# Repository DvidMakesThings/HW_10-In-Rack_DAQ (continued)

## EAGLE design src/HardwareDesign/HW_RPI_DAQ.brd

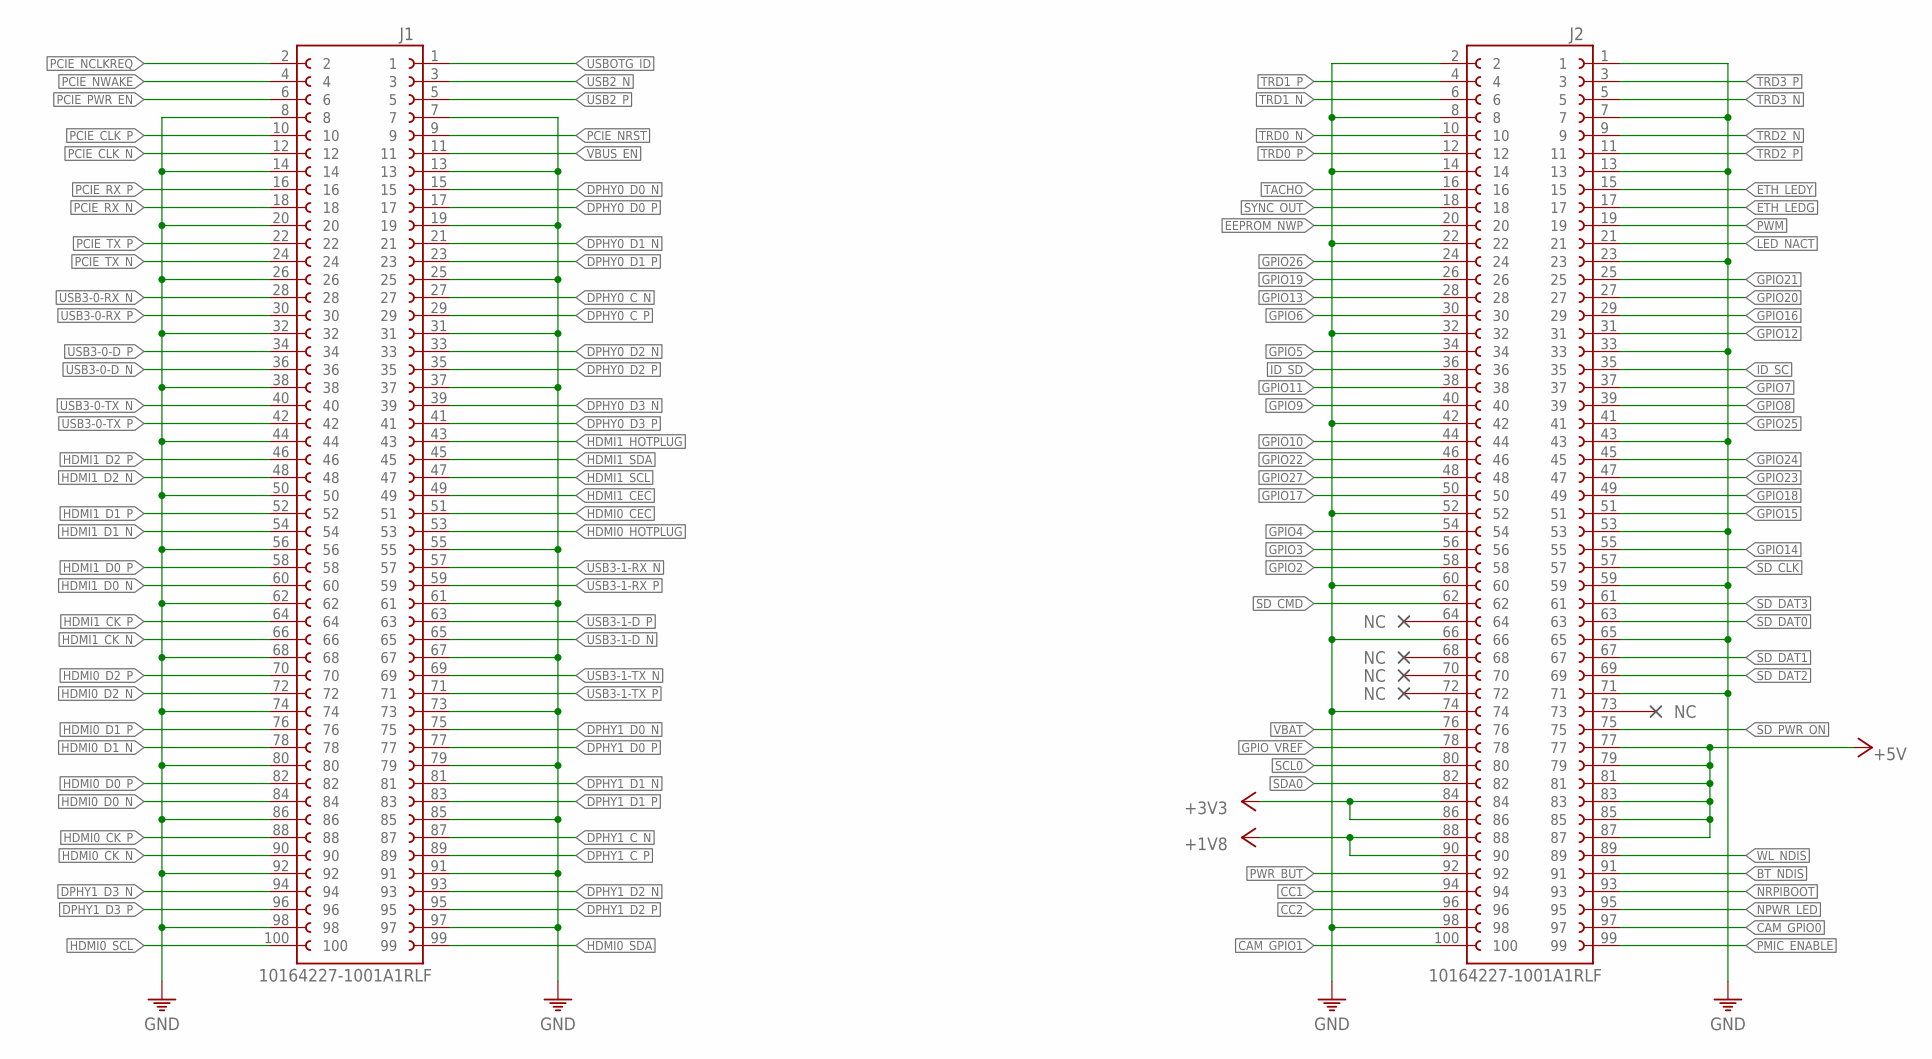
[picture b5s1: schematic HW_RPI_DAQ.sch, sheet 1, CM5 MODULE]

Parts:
J1, J2: 10164227-1001A1RLF; AMPHENOL_10164227-1001A1RLF

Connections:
+1V8: J2.88, J2.90; also elsewhere on the board
+3V3: J2.84, J2.86; also elsewhere on the board
+5V: J2.77, J2.79, J2.81, J2.83, J2.85, J2.87; also elsewhere on the board
BT_NDIS: J2.91; also elsewhere on the board
CAM_GPIO0: J2.97; also elsewhere on the board
CAM_GPIO1: J2.100; also elsewhere on the board
CC1: J2.94; also elsewhere on the board
CC2: J2.96; also elsewhere on the board
DPHY0_C_N: J1.27; also elsewhere on the board
DPHY0_C_P: J1.29; also elsewhere on the board
DPHY0_D0_N: J1.15; also elsewhere on the board
DPHY0_D0_P: J1.17; also elsewhere on the board
DPHY0_D1_N: J1.21; also elsewhere on the board
DPHY0_D1_P: J1.23; also elsewhere on the board
DPHY0_D2_N: J1.33; also elsewhere on the board
DPHY0_D2_P: J1.35; also elsewhere on the board
DPHY0_D3_N: J1.39; also elsewhere on the board
DPHY0_D3_P: J1.41; also elsewhere on the board
DPHY1_C_N: J1.87; also elsewhere on the board
DPHY1_C_P: J1.89; also elsewhere on the board
DPHY1_D0_N: J1.75; also elsewhere on the board
DPHY1_D0_P: J1.77; also elsewhere on the board
DPHY1_D1_N: J1.81; also elsewhere on the board
DPHY1_D1_P: J1.83; also elsewhere on the board
DPHY1_D2_N: J1.93; also elsewhere on the board
DPHY1_D2_P: J1.95; also elsewhere on the board
DPHY1_D3_N: J1.94; also elsewhere on the board
DPHY1_D3_P: J1.96; also elsewhere on the board
EEPROM_NWP: J2.20; also elsewhere on the board
ETH_LEDG: J2.17; also elsewhere on the board
ETH_LEDY: J2.15; also elsewhere on the board
GND: J1.7, J1.8, J1.13, J1.14, J1.19, J1.20, J1.25, J1.26, J1.31, J1.32, J1.37, J1.38, J1.44, J1.50, J1.55, J1.56, J1.61, J1.62, J1.67, J1.68, J1.73, J1.74, J1.79, J1.80, J1.85, J1.86, J1.91, J1.92, J1.97, J1.98, J2.1, J2.2, J2.7, J2.8, J2.13, J2.14, J2.22, J2.23, J2.32, J2.33, J2.42, J2.43, J2.52, J2.53, J2.59, J2.60, J2.65, J2.66, J2.71, J2.74, J2.98; also elsewhere on the board
GPIO2: J2.58; also elsewhere on the board
GPIO3: J2.56; also elsewhere on the board
GPIO4: J2.54; also elsewhere on the board
GPIO5: J2.34; also elsewhere on the board
GPIO6: J2.30; also elsewhere on the board
GPIO7: J2.37; also elsewhere on the board
GPIO8: J2.39; also elsewhere on the board
GPIO9: J2.40; also elsewhere on the board
GPIO10: J2.44; also elsewhere on the board
GPIO11: J2.38; also elsewhere on the board
GPIO12: J2.31; also elsewhere on the board
GPIO13: J2.28; also elsewhere on the board
GPIO14: J2.55; also elsewhere on the board
GPIO15: J2.51; also elsewhere on the board
GPIO16: J2.29; also elsewhere on the board
GPIO17: J2.50; also elsewhere on the board
GPIO18: J2.49; also elsewhere on the board
GPIO19: J2.26; also elsewhere on the board
GPIO20: J2.27; also elsewhere on the board
GPIO21: J2.25; also elsewhere on the board
GPIO22: J2.46; also elsewhere on the board
GPIO23: J2.47; also elsewhere on the board
GPIO24: J2.45; also elsewhere on the board
GPIO25: J2.41; also elsewhere on the board
GPIO26: J2.24; also elsewhere on the board
GPIO27: J2.48; also elsewhere on the board
GPIO_VREF: J2.78; also elsewhere on the board
HDMI0_CEC: J1.51; also elsewhere on the board
HDMI0_CK_N: J1.90; also elsewhere on the board
HDMI0_CK_P: J1.88; also elsewhere on the board
HDMI0_D0_N: J1.84; also elsewhere on the board
HDMI0_D0_P: J1.82; also elsewhere on the board
HDMI0_D1_N: J1.78; also elsewhere on the board
HDMI0_D1_P: J1.76; also elsewhere on the board
HDMI0_D2_N: J1.72; also elsewhere on the board
HDMI0_D2_P: J1.70; also elsewhere on the board
HDMI0_HOTPLUG: J1.53; also elsewhere on the board
HDMI0_SCL: J1.100; also elsewhere on the board
HDMI0_SDA: J1.99; also elsewhere on the board
HDMI1_CEC: J1.49; also elsewhere on the board
HDMI1_CK_N: J1.66; also elsewhere on the board
HDMI1_CK_P: J1.64; also elsewhere on the board
HDMI1_D0_N: J1.60; also elsewhere on the board
HDMI1_D0_P: J1.58; also elsewhere on the board
HDMI1_D1_N: J1.54; also elsewhere on the board
HDMI1_D1_P: J1.52; also elsewhere on the board
HDMI1_D2_N: J1.48; also elsewhere on the board
HDMI1_D2_P: J1.46; also elsewhere on the board
HDMI1_HOTPLUG: J1.43; also elsewhere on the board
HDMI1_SCL: J1.47; also elsewhere on the board
HDMI1_SDA: J1.45; also elsewhere on the board
ID_SC: J2.35; also elsewhere on the board
ID_SD: J2.36; also elsewhere on the board
LED_NACT: J2.21
NPWR_LED: J2.95; also elsewhere on the board
NRPIBOOT: J2.93; also elsewhere on the board
PCIE_CLK_N: J1.12; also elsewhere on the board
PCIE_CLK_P: J1.10; also elsewhere on the board
PCIE_NCLKREQ: J1.2; also elsewhere on the board
PCIE_NRST: J1.9; also elsewhere on the board
PCIE_NWAKE: J1.4; also elsewhere on the board
PCIE_PWR_EN: J1.6; also elsewhere on the board
PCIE_RX_N: J1.18; also elsewhere on the board
PCIE_RX_P: J1.16; also elsewhere on the board
PCIE_TX_N: J1.24; also elsewhere on the board
PCIE_TX_P: J1.22; also elsewhere on the board
PMIC_ENABLE: J2.99; also elsewhere on the board
PWM: J2.19; also elsewhere on the board
PWR_BUT: J2.92; also elsewhere on the board
SCL0: J2.80; also elsewhere on the board
SDA0: J2.82; also elsewhere on the board
SD_CLK: J2.57; also elsewhere on the board
SD_CMD: J2.62; also elsewhere on the board
SD_DAT0: J2.63; also elsewhere on the board
SD_DAT1: J2.67; also elsewhere on the board
SD_DAT2: J2.69; also elsewhere on the board
SD_DAT3: J2.61; also elsewhere on the board
SD_PWR_ON: J2.75; also elsewhere on the board
SYNC_OUT: J2.18; also elsewhere on the board
TACHO: J2.16; also elsewhere on the board
TRD0_N: J2.10; also elsewhere on the board
TRD0_P: J2.12; also elsewhere on the board
TRD1_N: J2.6; also elsewhere on the board
TRD1_P: J2.4; also elsewhere on the board
TRD2_N: J2.9; also elsewhere on the board
TRD2_P: J2.11; also elsewhere on the board
TRD3_N: J2.5; also elsewhere on the board
TRD3_P: J2.3; also elsewhere on the board
USB2_N: J1.3; also elsewhere on the board
USB2_P: J1.5; also elsewhere on the board
USB3-0-D_N: J1.36; also elsewhere on the board
USB3-0-D_P: J1.34; also elsewhere on the board
USB3-0-RX_N: J1.28; also elsewhere on the board
USB3-0-RX_P: J1.30; also elsewhere on the board
USB3-0-TX_N: J1.40; also elsewhere on the board
USB3-0-TX_P: J1.42; also elsewhere on the board
USB3-1-D_N: J1.65; also elsewhere on the board
USB3-1-D_P: J1.63; also elsewhere on the board
USB3-1-RX_N: J1.57; also elsewhere on the board
USB3-1-RX_P: J1.59; also elsewhere on the board
USB3-1-TX_N: J1.69; also elsewhere on the board
USB3-1-TX_P: J1.71; also elsewhere on the board
USBOTG_ID: J1.1; also elsewhere on the board
VBAT: J2.76; also elsewhere on the board
VBUS_EN: J1.11; also elsewhere on the board
WL_NDIS: J2.89; also elsewhere on the board

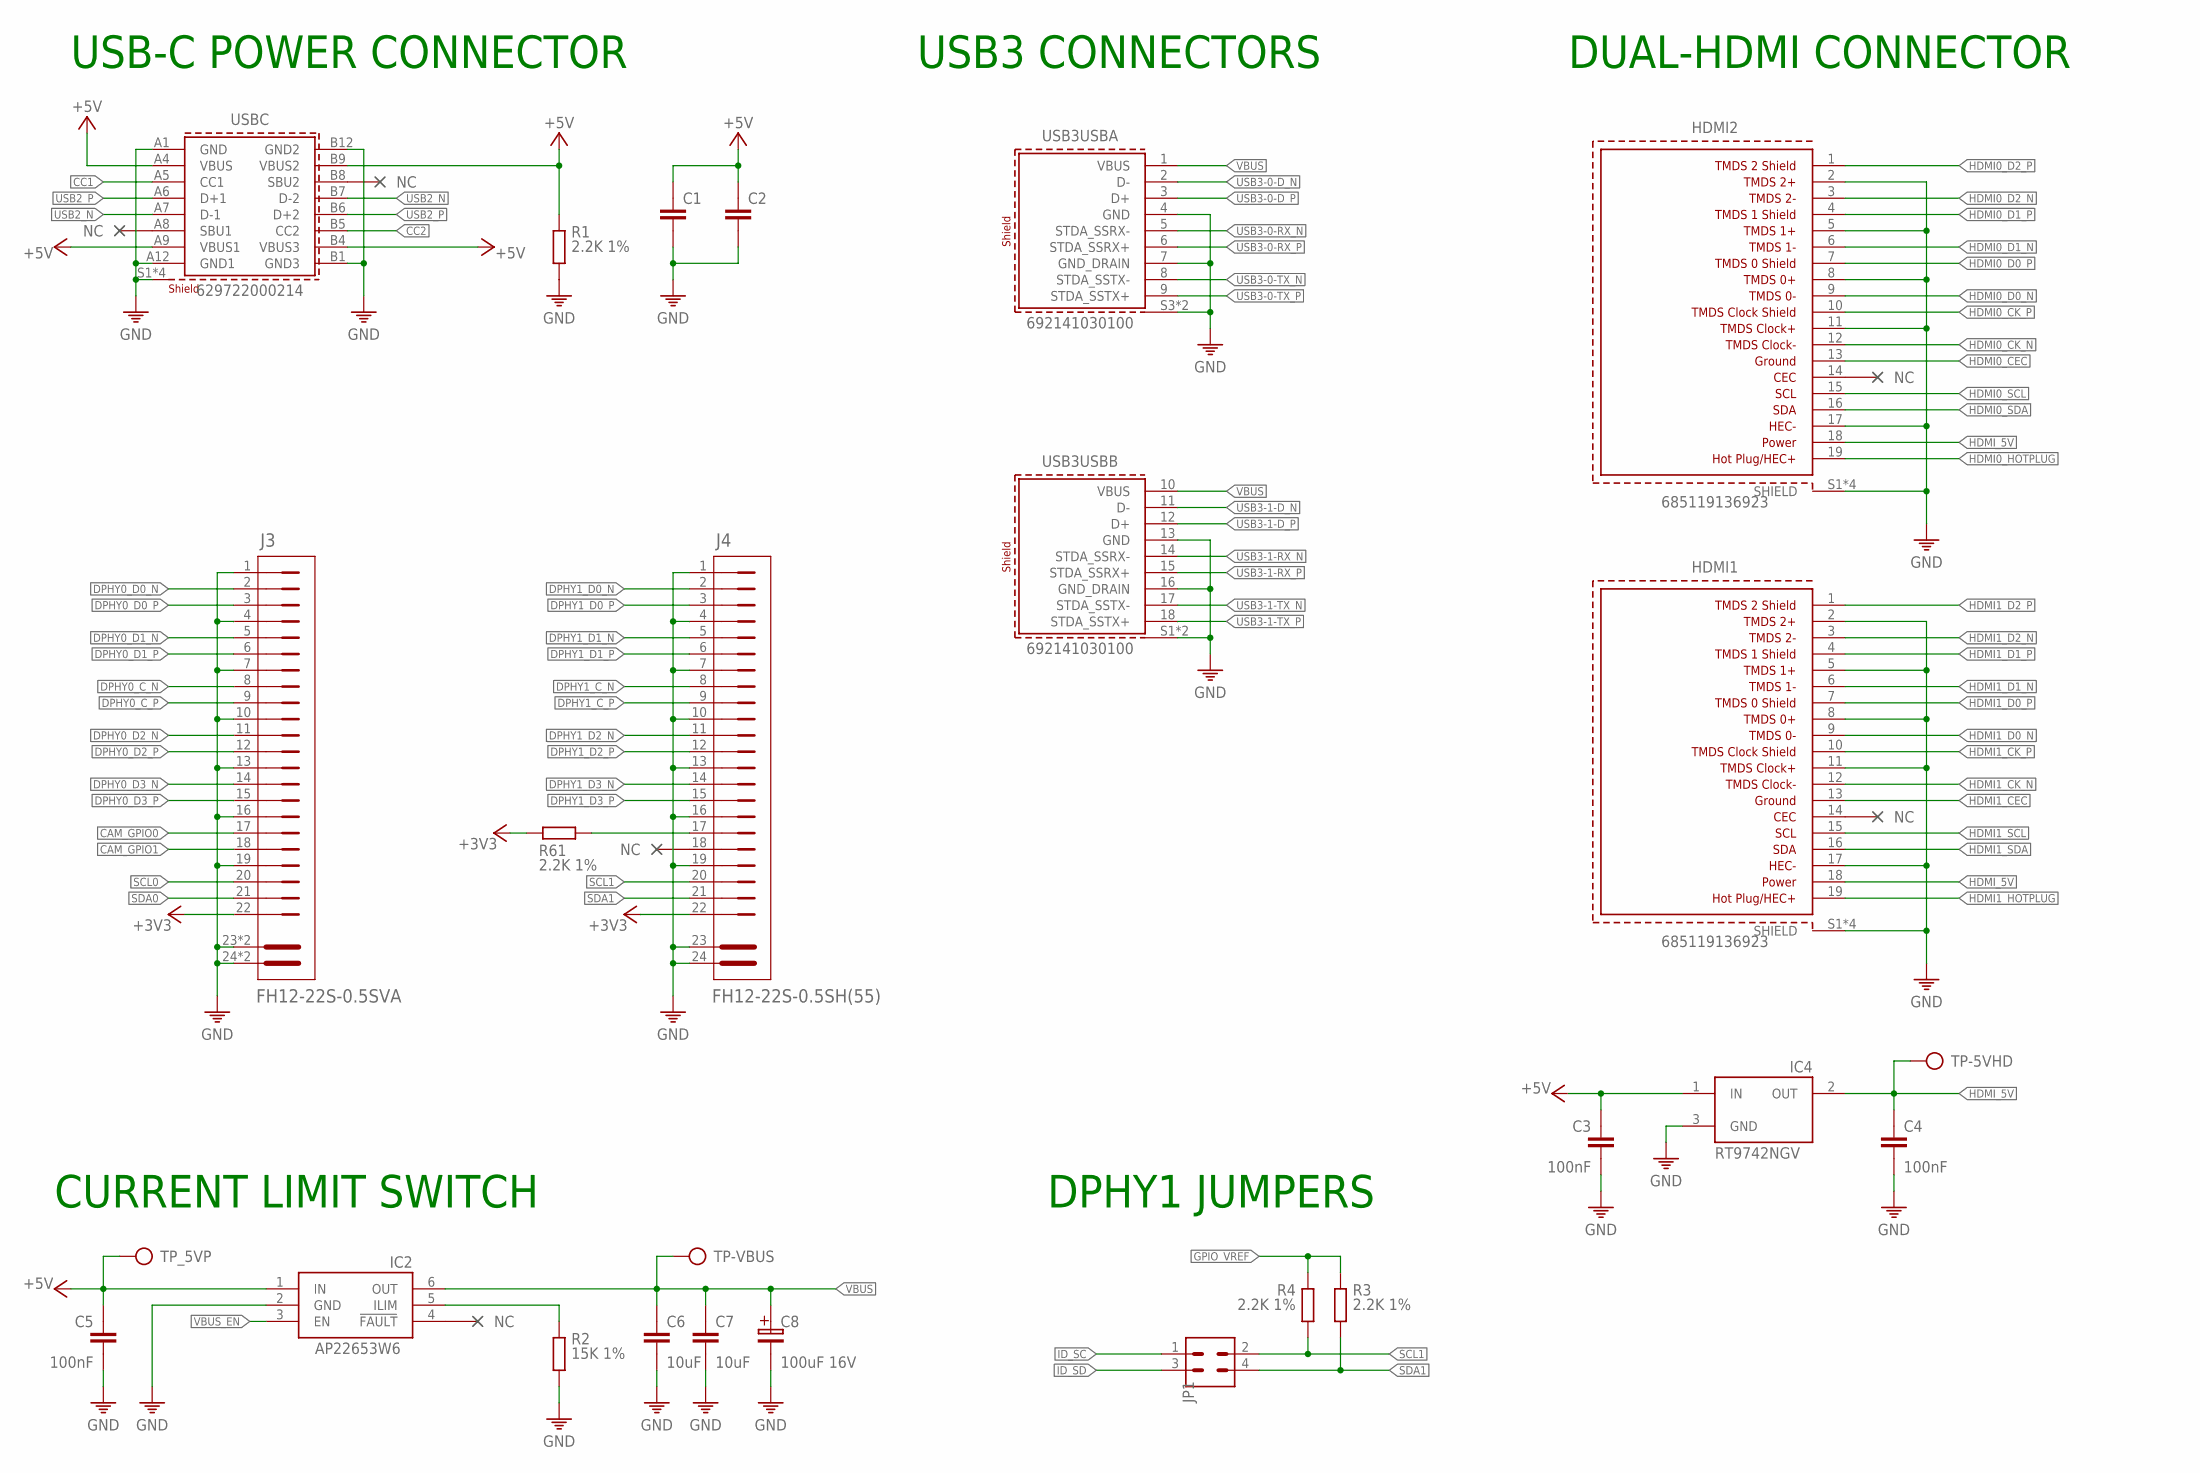
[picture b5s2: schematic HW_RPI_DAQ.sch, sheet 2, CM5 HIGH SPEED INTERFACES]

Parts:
C1, C2: C0402; 0402
C3, C4, C5: 100nF; 0402
C6, C7: 10uF; 0805
C8: 100uF 16V; 100UF-16V
HDMI1, HDMI2: 685119136923
IC2: AP22653W6; SOT23-6
IC4: RT9742NGV; SOT23
J3: FH12-22S-0.5SVA; FH12-22S-0.5SH
J4: FH12-22S-0.5SH(55); CONN_FH12-22S-0.5SH(55)_HIR
JP1: CON-2X2; 2X2
R1, R3, R4, R61: 2.2K 1%; 0402
R2: 15K 1%; 0402
TP-5VHD: TP
TP-VBUS: TP
TP_5VP: TP
USB3: 692141030100
USBC: 629722000214

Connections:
+3V3: J3.22, J4.22, R61.2; also elsewhere on the board
+5V: C1.1, C2.1, C3.1, C5.1, IC2.1 (IN), IC4.1 (IN), R1.1, TP_5VP.TP, USBC.A4 (VBUS), USBC.A9 (VBUS1), USBC.B4 (VBUS3), USBC.B9 (VBUS2); also elsewhere on the board
CAM_GPIO0: J3.17; also elsewhere on the board
CAM_GPIO1: J3.18; also elsewhere on the board
CC1: USBC.A5 (CC1); also elsewhere on the board
CC2: USBC.B5 (CC2); also elsewhere on the board
DPHY0_C_N: J3.8; also elsewhere on the board
DPHY0_C_P: J3.9; also elsewhere on the board
DPHY0_D0_N: J3.2; also elsewhere on the board
DPHY0_D0_P: J3.3; also elsewhere on the board
DPHY0_D1_N: J3.5; also elsewhere on the board
DPHY0_D1_P: J3.6; also elsewhere on the board
DPHY0_D2_N: J3.11; also elsewhere on the board
DPHY0_D2_P: J3.12; also elsewhere on the board
DPHY0_D3_N: J3.14; also elsewhere on the board
DPHY0_D3_P: J3.15; also elsewhere on the board
DPHY1_C_N: J4.8; also elsewhere on the board
DPHY1_C_P: J4.9; also elsewhere on the board
DPHY1_D0_N: J4.2; also elsewhere on the board
DPHY1_D0_P: J4.3; also elsewhere on the board
DPHY1_D1_N: J4.5; also elsewhere on the board
DPHY1_D1_P: J4.6; also elsewhere on the board
DPHY1_D2_N: J4.11; also elsewhere on the board
DPHY1_D2_P: J4.12; also elsewhere on the board
DPHY1_D3_N: J4.14; also elsewhere on the board
DPHY1_D3_P: J4.15; also elsewhere on the board
GND: C1.2, C2.2, C3.2, C4.2, C5.2, C6.2, C7.2, C8.2, HDMI1.2 (TMDS2+), HDMI1.5 (TMDSDATA1+), HDMI1.8 (TMDS0+), HDMI1.11 (TMDSCLOCK+), HDMI1.17 (UTILITY/HEAC+), HDMI1.S1 (SHIELD), HDMI1.S2 (SHIELD), HDMI1.S3 (SHIELD), HDMI1.S4 (SHIELD), HDMI2.2 (TMDS2+), HDMI2.5 (TMDSDATA1+), HDMI2.8 (TMDS0+), HDMI2.11 (TMDSCLOCK+), HDMI2.17 (UTILITY/HEAC+), HDMI2.S1 (SHIELD), HDMI2.S2 (SHIELD), HDMI2.S3 (SHIELD), HDMI2.S4 (SHIELD), IC2.2 (GND), IC4.3 (GND), J3.1, J3.4, J3.7, J3.10, J3.13, J3.16, J3.19, J3.23 (MH1), J3.24 (MH2), J3.25 (MH1), J3.26 (MH2), J4.1, J4.4, J4.7, J4.10, J4.13, J4.16, J4.19, J4.23 (MH1), J4.24 (MH2), R1.2, R2.2, USB3.4 (GND), USB3.7 (GND_DRAIN), USB3.13 (GND), USB3.16 (GND_DRAIN), USB3.S1 (SHIELD), USB3.S2 (SHIELD), USB3.S3 (SHIELD), USB3.S4 (SHIELD), USBC.A1 (GND), USBC.A12 (GND1), USBC.B1 (GND3), USBC.B12 (GND2), USBC.S1 (SHIELD), USBC.S2 (SHIELD), USBC.S3 (SHIELD), USBC.S4 (SHIELD); also elsewhere on the board
GPIO_VREF: R3.1, R4.1; also elsewhere on the board
HDMI0_CEC: HDMI2.13 (GROUND); also elsewhere on the board
HDMI0_CK_N: HDMI2.12 (TMDSCLOCK-); also elsewhere on the board
HDMI0_CK_P: HDMI2.10 (TMDSCLOCKSHIELD); also elsewhere on the board
HDMI0_D0_N: HDMI2.9 (TMDS0-); also elsewhere on the board
HDMI0_D0_P: HDMI2.7 (TMDS0SHIELD); also elsewhere on the board
HDMI0_D1_N: HDMI2.6 (TMDS1-); also elsewhere on the board
HDMI0_D1_P: HDMI2.4 (TMDS1SHIELD); also elsewhere on the board
HDMI0_D2_N: HDMI2.3 (TMDS2-); also elsewhere on the board
HDMI0_D2_P: HDMI2.1 (TMDS2SHIELD); also elsewhere on the board
HDMI0_HOTPLUG: HDMI2.19 (HOTPLUG/HEC+); also elsewhere on the board
HDMI0_SCL: HDMI2.15 (SCL); also elsewhere on the board
HDMI0_SDA: HDMI2.16 (SDA); also elsewhere on the board
HDMI1_CEC: HDMI1.13 (GROUND); also elsewhere on the board
HDMI1_CK_N: HDMI1.12 (TMDSCLOCK-); also elsewhere on the board
HDMI1_CK_P: HDMI1.10 (TMDSCLOCKSHIELD); also elsewhere on the board
HDMI1_D0_N: HDMI1.9 (TMDS0-); also elsewhere on the board
HDMI1_D0_P: HDMI1.7 (TMDS0SHIELD); also elsewhere on the board
HDMI1_D1_N: HDMI1.6 (TMDS1-); also elsewhere on the board
HDMI1_D1_P: HDMI1.4 (TMDS1SHIELD); also elsewhere on the board
HDMI1_D2_N: HDMI1.3 (TMDS2-); also elsewhere on the board
HDMI1_D2_P: HDMI1.1 (TMDS2SHIELD); also elsewhere on the board
HDMI1_HOTPLUG: HDMI1.19 (HOTPLUG/HEC+); also elsewhere on the board
HDMI1_SCL: HDMI1.15 (SCL); also elsewhere on the board
HDMI1_SDA: HDMI1.16 (SDA); also elsewhere on the board
HDMI_5V: C4.1, HDMI1.18 (POWER), HDMI2.18 (POWER), IC4.2 (OUT), TP-5VHD.TP
ID_SC: JP1.1; also elsewhere on the board
ID_SD: JP1.3; also elsewhere on the board
unnamed: IC2.5 (ILIM), R2.1
unnamed: J4.17, R61.1
SCL0: J3.20; also elsewhere on the board
SCL1: J4.20, JP1.2, R4.2
SDA0: J3.21; also elsewhere on the board
SDA1: J4.21, JP1.4, R3.2
USB2_N: USBC.A7 (D-1), USBC.B7 (D-2); also elsewhere on the board
USB2_P: USBC.A6 (D+1), USBC.B6 (D+2); also elsewhere on the board
USB3-0-D_N: USB3.2 (D-); also elsewhere on the board
USB3-0-D_P: USB3.3 (D+); also elsewhere on the board
USB3-0-RX_N: USB3.5 (STDA_SSRX-); also elsewhere on the board
USB3-0-RX_P: USB3.6 (STDA_SSRX+); also elsewhere on the board
USB3-0-TX_N: USB3.8 (STDA_SSTX-); also elsewhere on the board
USB3-0-TX_P: USB3.9 (STDA_SSTX+); also elsewhere on the board
USB3-1-D_N: USB3.11 (D-); also elsewhere on the board
USB3-1-D_P: USB3.12 (D+); also elsewhere on the board
USB3-1-RX_N: USB3.14 (STDA_SSRX-); also elsewhere on the board
USB3-1-RX_P: USB3.15 (STDA_SSRX+); also elsewhere on the board
USB3-1-TX_N: USB3.17 (STDA_SSTX-); also elsewhere on the board
USB3-1-TX_P: USB3.18 (STDA_SSTX+); also elsewhere on the board
VBUS: C6.1, C7.1, C8.1, IC2.6 (OUT), TP-VBUS.TP, USB3.1 (VBUS), USB3.10 (VBUS)
VBUS_EN: IC2.3 (EN); also elsewhere on the board

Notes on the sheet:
USB-C POWER CONNECTOR
USB3 CONNECTORS
DUAL-HDMI CONNECTOR
CURRENT LIMIT SWITCH
DPHY1 JUMPERS

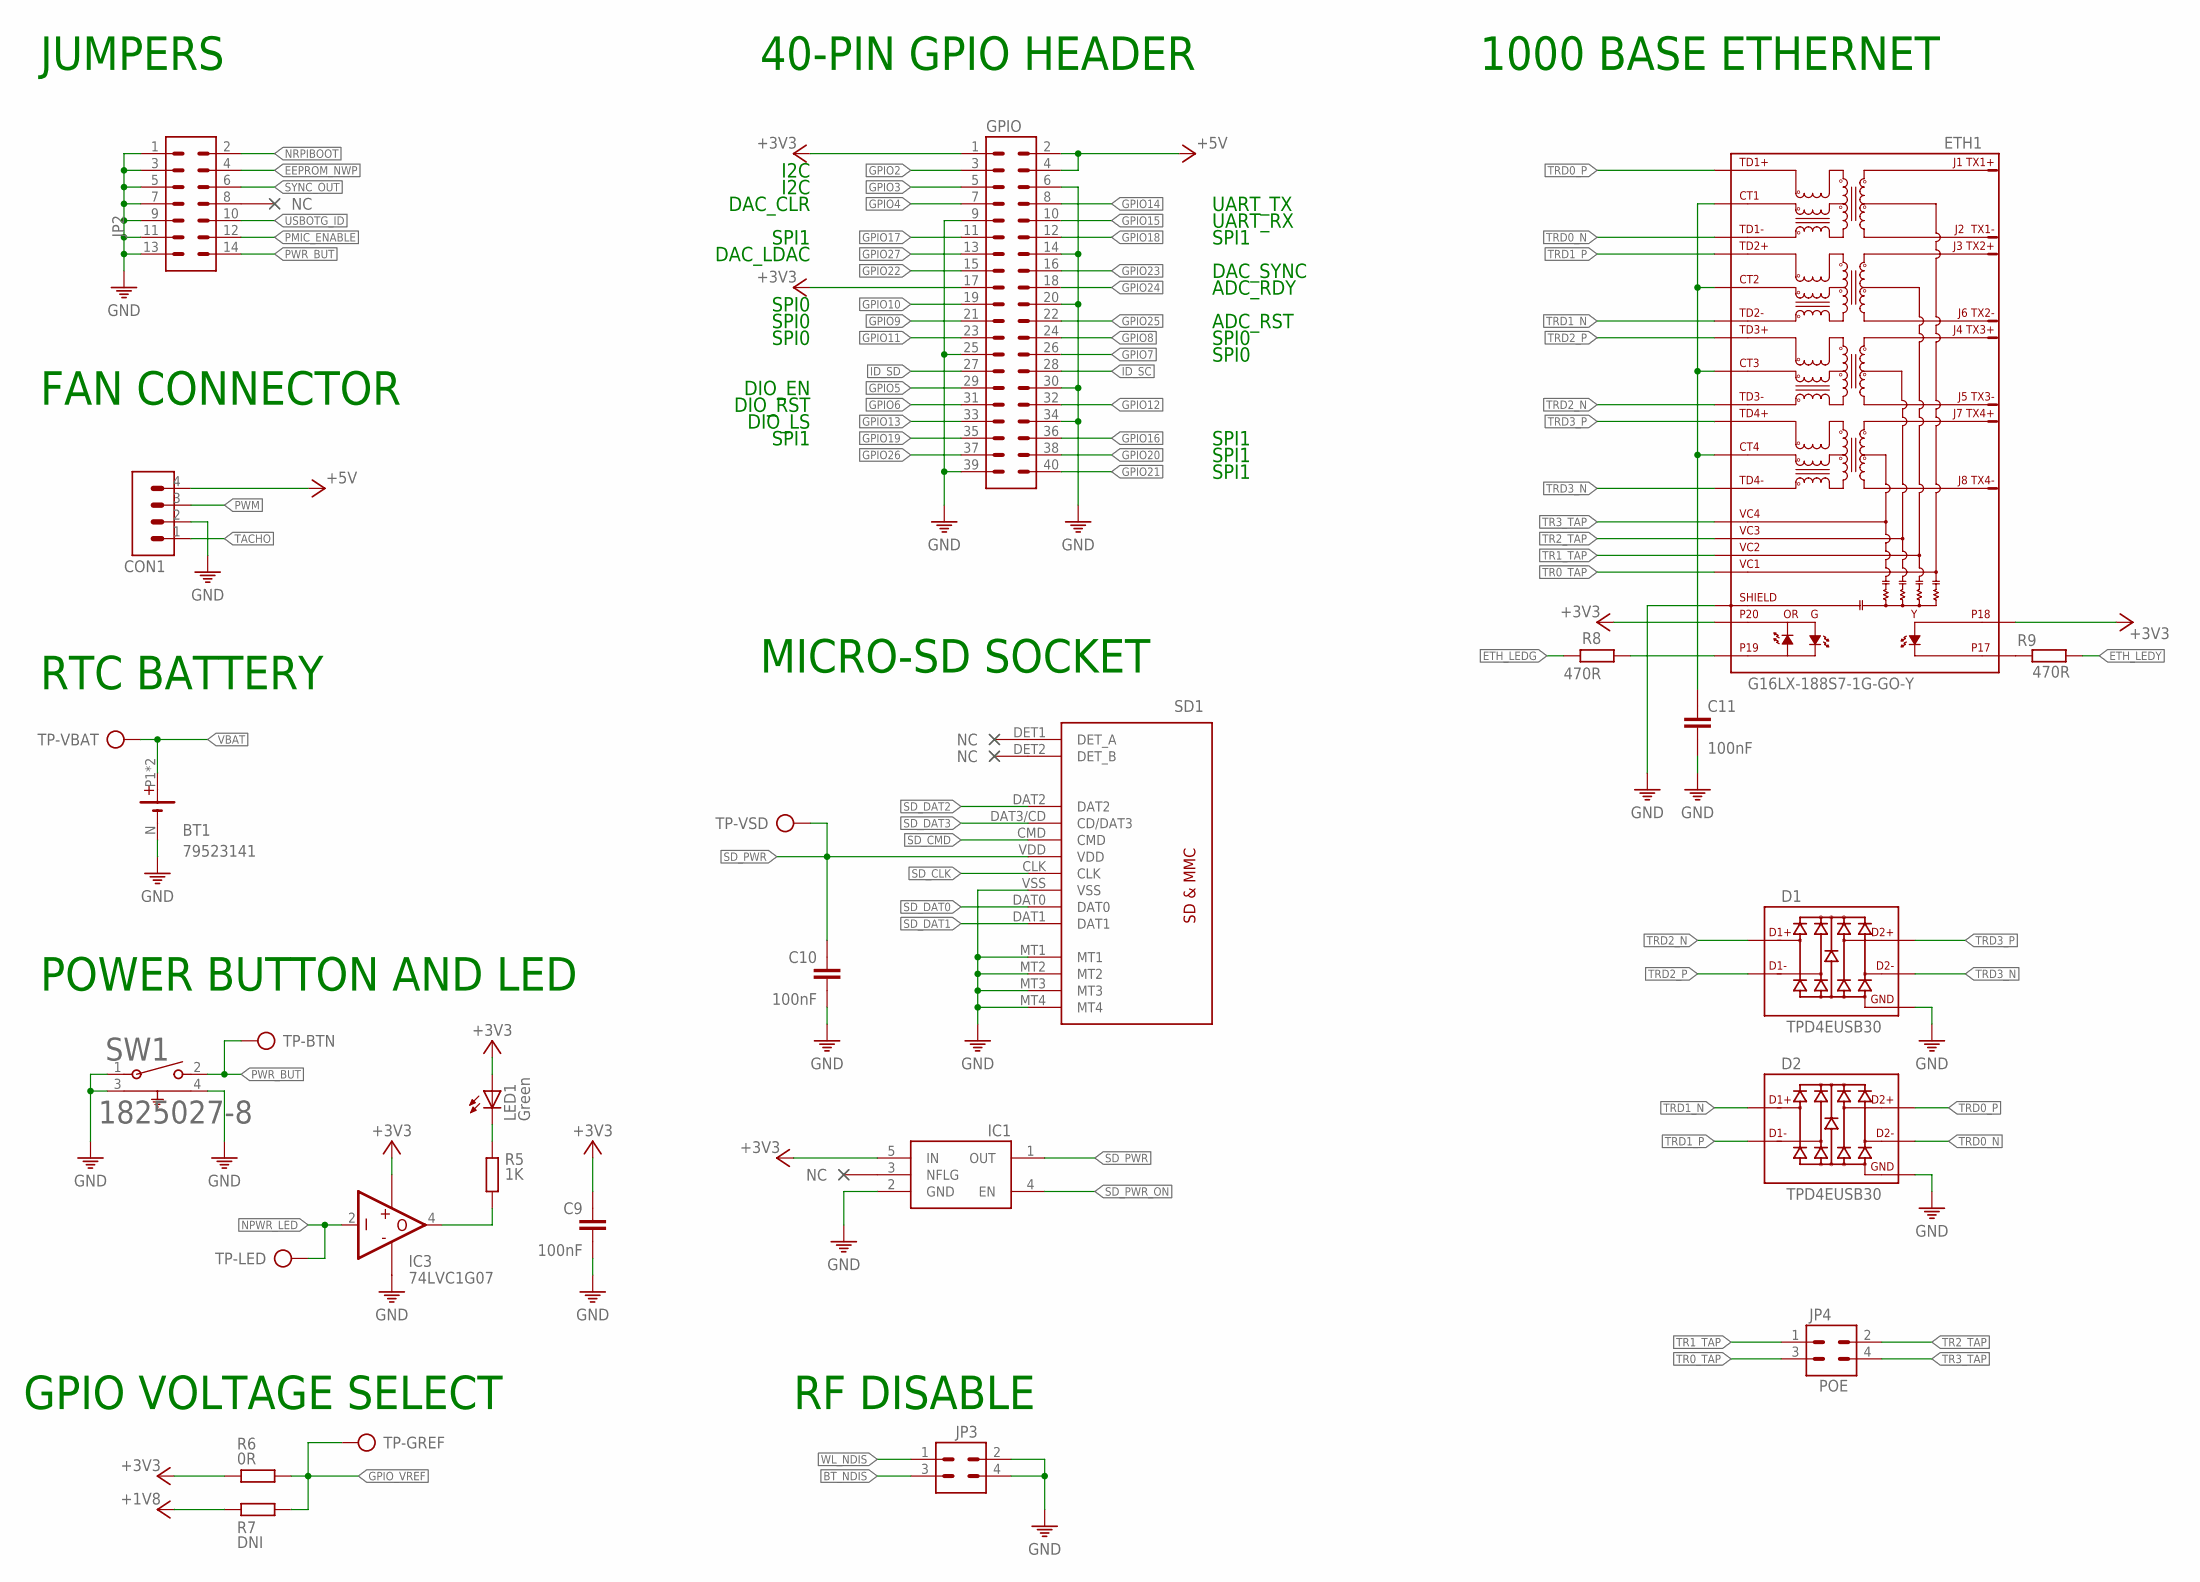
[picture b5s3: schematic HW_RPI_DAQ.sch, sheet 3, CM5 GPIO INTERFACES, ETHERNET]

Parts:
BT1: 79523141
C9, C10, C11: 100nF; 0402
CON1: CON-1X4; 1X4
D1, D2: TPD4EUSB30; USON
ETH1: G16LX-188S7-1G-GO-Y; MAGJACK_POE
GPIO: CON-2X20; 2X20
IC1: RT9742GGJ5; SOT23-5
IC3: 74LVC1G07; SOT23-5
JP2: CON-2X7; 2X7
JP3: CON-2X2; 2X2
JP4: POE; 2X2
LED1: Green; CHIPLED_0805
R5: 1K; 0402
R6: 0R; 0402
R7: DNI; 0402
R8, R9: 470R; 0402
SD1: MICRO-SD; MICROSD
SW1: 1825027-8; SW2_1825027-C_TEC
TP-BTN: TP
TP-GREF: TP
TP-LED: TP
TP-VBAT: TP
TP-VSD: TP

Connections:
+1V8: R7.1; also elsewhere on the board
+3V3: C9.1, ETH1.18, ETH1.20, GPIO.1, GPIO.17, IC1.5 (IN), IC3.5 (VCC), LED1.A, R6.1; also elsewhere on the board
+5V: CON1.4, GPIO.2, GPIO.4; also elsewhere on the board
BT_NDIS: JP3.3; also elsewhere on the board
EEPROM_NWP: JP2.4; also elsewhere on the board
ETH_LEDG: R8.1; also elsewhere on the board
ETH_LEDY: R9.2; also elsewhere on the board
GND: BT1.N (-), C9.2, C10.2, C11.2, CON1.2, D1.3 (GND), D1.8 (GND), D2.3 (GND), D2.8 (GND), ETH1.MH3 (SHIELD), ETH1.MH4 (SHIELD), GPIO.6, GPIO.9, GPIO.14, GPIO.20, GPIO.25, GPIO.30, GPIO.34, GPIO.39, IC1.2 (GND), IC3.3 (GND), JP2.1, JP2.3, JP2.5, JP2.7, JP2.9, JP2.11, JP2.13, JP3.2, JP3.4, SD1.MT1, SD1.MT2, SD1.MT3, SD1.MT4, SD1.VSS, SW1.1, SW1.3, SW1.4; also elsewhere on the board
GPIO2: GPIO.3; also elsewhere on the board
GPIO3: GPIO.5; also elsewhere on the board
GPIO4: GPIO.7; also elsewhere on the board
GPIO5: GPIO.29; also elsewhere on the board
GPIO6: GPIO.31; also elsewhere on the board
GPIO7: GPIO.26; also elsewhere on the board
GPIO8: GPIO.24; also elsewhere on the board
GPIO9: GPIO.21; also elsewhere on the board
GPIO10: GPIO.19; also elsewhere on the board
GPIO11: GPIO.23; also elsewhere on the board
GPIO12: GPIO.32; also elsewhere on the board
GPIO13: GPIO.33; also elsewhere on the board
GPIO14: GPIO.8; also elsewhere on the board
GPIO15: GPIO.10; also elsewhere on the board
GPIO16: GPIO.36; also elsewhere on the board
GPIO17: GPIO.11; also elsewhere on the board
GPIO18: GPIO.12; also elsewhere on the board
GPIO19: GPIO.35; also elsewhere on the board
GPIO20: GPIO.38; also elsewhere on the board
GPIO21: GPIO.40; also elsewhere on the board
GPIO22: GPIO.15; also elsewhere on the board
GPIO23: GPIO.16; also elsewhere on the board
GPIO24: GPIO.18; also elsewhere on the board
GPIO25: GPIO.22; also elsewhere on the board
GPIO26: GPIO.37; also elsewhere on the board
GPIO27: GPIO.13; also elsewhere on the board
GPIO_VREF: R6.2, R7.2, TP-GREF.TP; also elsewhere on the board
ID_SC: GPIO.28; also elsewhere on the board
ID_SD: GPIO.27; also elsewhere on the board
unnamed: LED1.C, R5.1
unnamed: IC3.4 (Y), R5.2
unnamed: C11.1, ETH1.CT1, ETH1.CT2, ETH1.CT3, ETH1.CT4
unnamed: ETH1.17, R9.1
unnamed: ETH1.19, R8.2
NPWR_LED: IC3.2 (A), TP-LED.TP; also elsewhere on the board
NRPIBOOT: JP2.2; also elsewhere on the board
PMIC_ENABLE: JP2.12; also elsewhere on the board
PWM: CON1.3; also elsewhere on the board
PWR_BUT: JP2.14, SW1.2, TP-BTN.TP; also elsewhere on the board
SD_CLK: SD1.CLK; also elsewhere on the board
SD_CMD: SD1.CMD; also elsewhere on the board
SD_DAT0: SD1.DAT0; also elsewhere on the board
SD_DAT1: SD1.DAT1; also elsewhere on the board
SD_DAT2: SD1.DAT2; also elsewhere on the board
SD_DAT3: SD1.DAT3/CD (CD/DAT3); also elsewhere on the board
SD_PWR: C10.1, IC1.1 (OUT), SD1.VDD, TP-VSD.TP
SD_PWR_ON: IC1.4 (EN); also elsewhere on the board
SYNC_OUT: JP2.6; also elsewhere on the board
TACHO: CON1.1; also elsewhere on the board
TR0_TAP: ETH1.VC1, JP4.3
TR1_TAP: ETH1.VC2, JP4.1
TR2_TAP: ETH1.VC3, JP4.2
TR3_TAP: ETH1.VC4, JP4.4
TRD0_N: D2.2 (D1-), D2.9 (D1-), ETH1.TD1-; also elsewhere on the board
TRD0_P: D2.1 (D1+), D2.10 (D1+), ETH1.TD1+; also elsewhere on the board
TRD1_N: D2.4 (D2+), D2.7 (D2+), ETH1.TD2-; also elsewhere on the board
TRD1_P: D2.5 (D2-), D2.6 (D2-), ETH1.TD2+; also elsewhere on the board
TRD2_N: D1.4 (D2+), D1.7 (D2+), ETH1.TD3-; also elsewhere on the board
TRD2_P: D1.5 (D2-), D1.6 (D2-), ETH1.TD3+; also elsewhere on the board
TRD3_N: D1.2 (D1-), D1.9 (D1-), ETH1.TD4-; also elsewhere on the board
TRD3_P: D1.1 (D1+), D1.10 (D1+), ETH1.TD4+; also elsewhere on the board
USBOTG_ID: JP2.10; also elsewhere on the board
VBAT: BT1.P1 (+), BT1.P2 (+), TP-VBAT.TP; also elsewhere on the board
WL_NDIS: JP3.1; also elsewhere on the board

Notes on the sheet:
JUMPERS
FAN CONNECTOR
RTC BATTERY
POWER BUTTON AND LED
GPIO VOLTAGE SELECT
40-PIN GPIO HEADER
MICRO-SD SOCKET
1000 BASE ETHERNET
RF DISABLE
SPI0
SPI1
I2C
ADC_RDY
DAC_LDAC
DAC_SYNC
DAC_CLR
ADC_RST
DIO_RST
DIO_LS
DIO_EN
UART_TX
UART_RX
